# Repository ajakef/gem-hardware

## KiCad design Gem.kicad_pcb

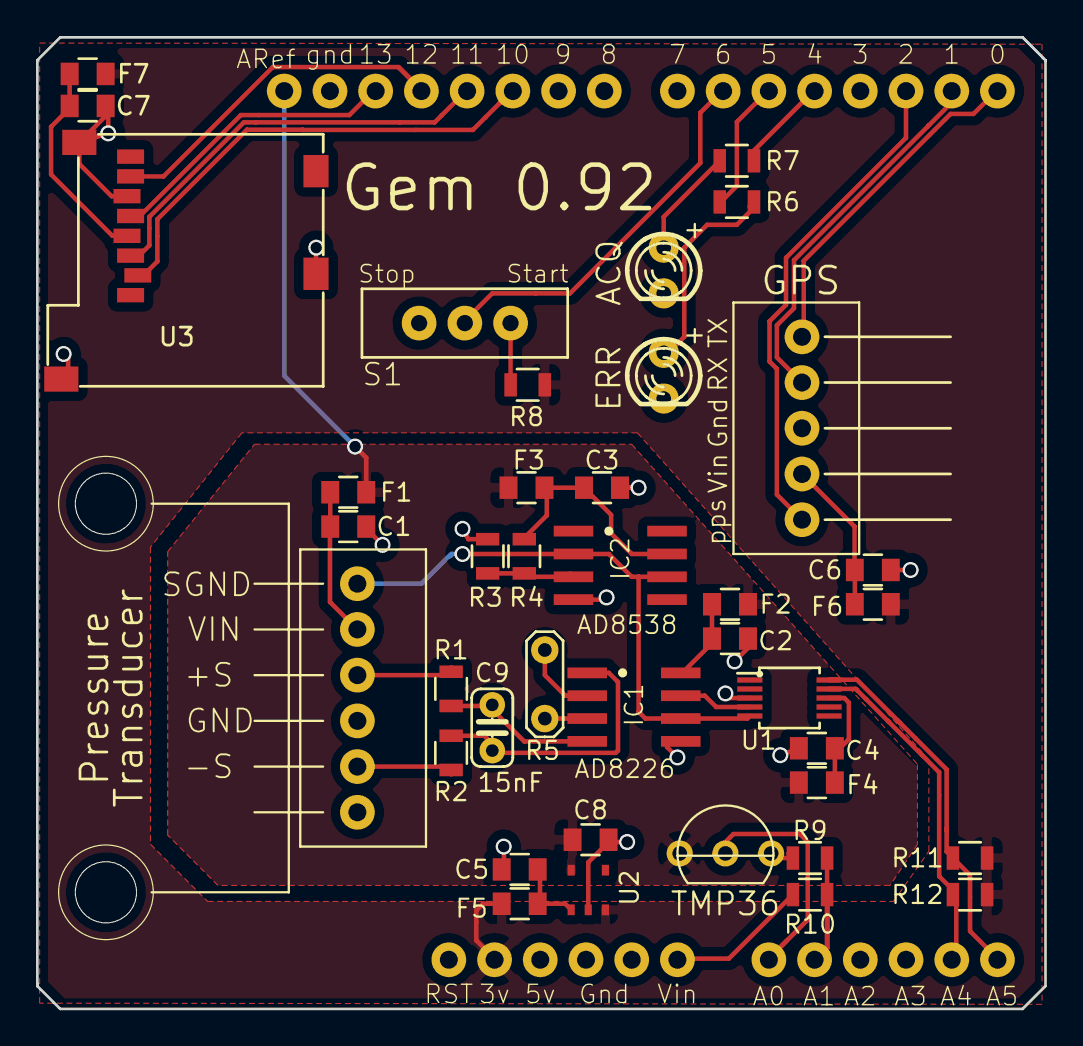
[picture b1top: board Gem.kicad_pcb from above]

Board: 2 copper layers, 56.0 x 54.0 mm, 40 parts (0 on the bottom side), 37 nets.

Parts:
C1, C2, C3, C4, C5, C6, C7: 0.1uF; C_0805
C8: 22 uF; C_0805
C9: 15nF; C025-024X044
F1, F2, F3, F4, F5, F6, F7: FB; C_0805
IC1: AD8226; SO8
IC2: AD8538; SO8
M1: ALLSENSORS-A6AAF-CUTLEADS
M2: Board; ARDUINO-NOHOLE-DIM_ON_BDOCU_ONLY
M6: ADAFRUIT-GPS; ADAFRUIT-ULTIMATE-GPS-MOD
R1, R2, R3, R4: 47k; R_0805
R5: 2.2k; R-TH-VERT
R6, R7, R8: 470; R_0805
R9: 22k; R_0805
R10: 100k; R_0805
R11, R12: 2.2k; R_0805
S1: EG1218
TMP36: TMP36; TO92-EBC-OVAL
U1: ADS1115; MSOP-10_3x3mm_Pitch0.5mm
U2: TCR2EF; SC-74A
U3: Micro-SD
blue1: ACQ; LED3MM
red1: ERR; LED3MM

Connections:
+1V5: IC1.6, IC2.2, IC2.6, M1.1, U1.5
+3V3: F5.1, F6.1, F7.2, M2.3V, R8.2, R11.1, R12.2, U2.3
+BATT: M2.VIN, R10.1
/N$2: IC1.7, U1.4
/N$3: M1.S-, R2.1
/N$4: C9.2, IC1.4, R1.2
/N$5: IC1.3, R5.1
/N$6: IC1.2, R5.2
/N$7: M1.S+, R1.1
/N$8: IC2.3, R3.2, R4.1
/N$9: C9.1, IC1.1, R2.2
/N$11: M2.D10, U3.2
/N$12: M2.D11, U3.3
/N$13: M2.D12, U3.7
/N$14: M2.D13, U3.5
/N$15: M2.D1, M6.P$RX
/N$16: M2.D0, M6.P$TX
/N$17: M2.D5, R6.1
/N$18: M2.D2, M6.P$PP
/N$19: M2.D6, S1.P
/N$20: M2.A4, R12.1, U1.9
/N$21: M2.D4, R7.1
/N$22: R6.2, red1.A
/N$23: R7.2, blue1.A
/N$24: M2.A5, R11.2, U1.10
/N$25: M2.A0, TMP36.B
/N$26: R8.1, S1.O
/N$27: M2.A1, R9.1, R10.2
/N$28: C6.2, F6.2, M6.P$VI
/N$29: C3.1, F3.2, IC2.7, R4.2
/N$31: C2.1, F2.1, IC1.8
/N$32: C1.1, F1.1, M1.VIN
GND: C1.2, C2.2, C3.2, C4.1, C5.1, C6.1, C7.1, C8.2, IC1.5, IC2.4, M1.GND, M2.GND, M2.GND1, M2.GND2, M6.P$GN, R3.1, R9.2, S1.S, TMP36.C, U1.3, U2.2, U3.6, blue1.K, red1.K
unnamed: C4.2, F4.2, U1.8
unnamed: C5.2, F5.2, U2.1
unnamed: C7.2, F7.1, U3.4
VAA: C8.1, F1.2, F2.2, F3.1, F4.1, M2.AREF, TMP36.E, U2.5

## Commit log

2018-01-03 v0.82, first version for github
2018-01-03 v0.83, last version using Diavolino
2018-01-03 v0.9, first version using Efficientino
2018-01-03 v0.91
2018-01-03 v0.92, version of SRL paper
2018-01-03 v0.92, libraries fixed
2018-01-03 Create LICENSE
